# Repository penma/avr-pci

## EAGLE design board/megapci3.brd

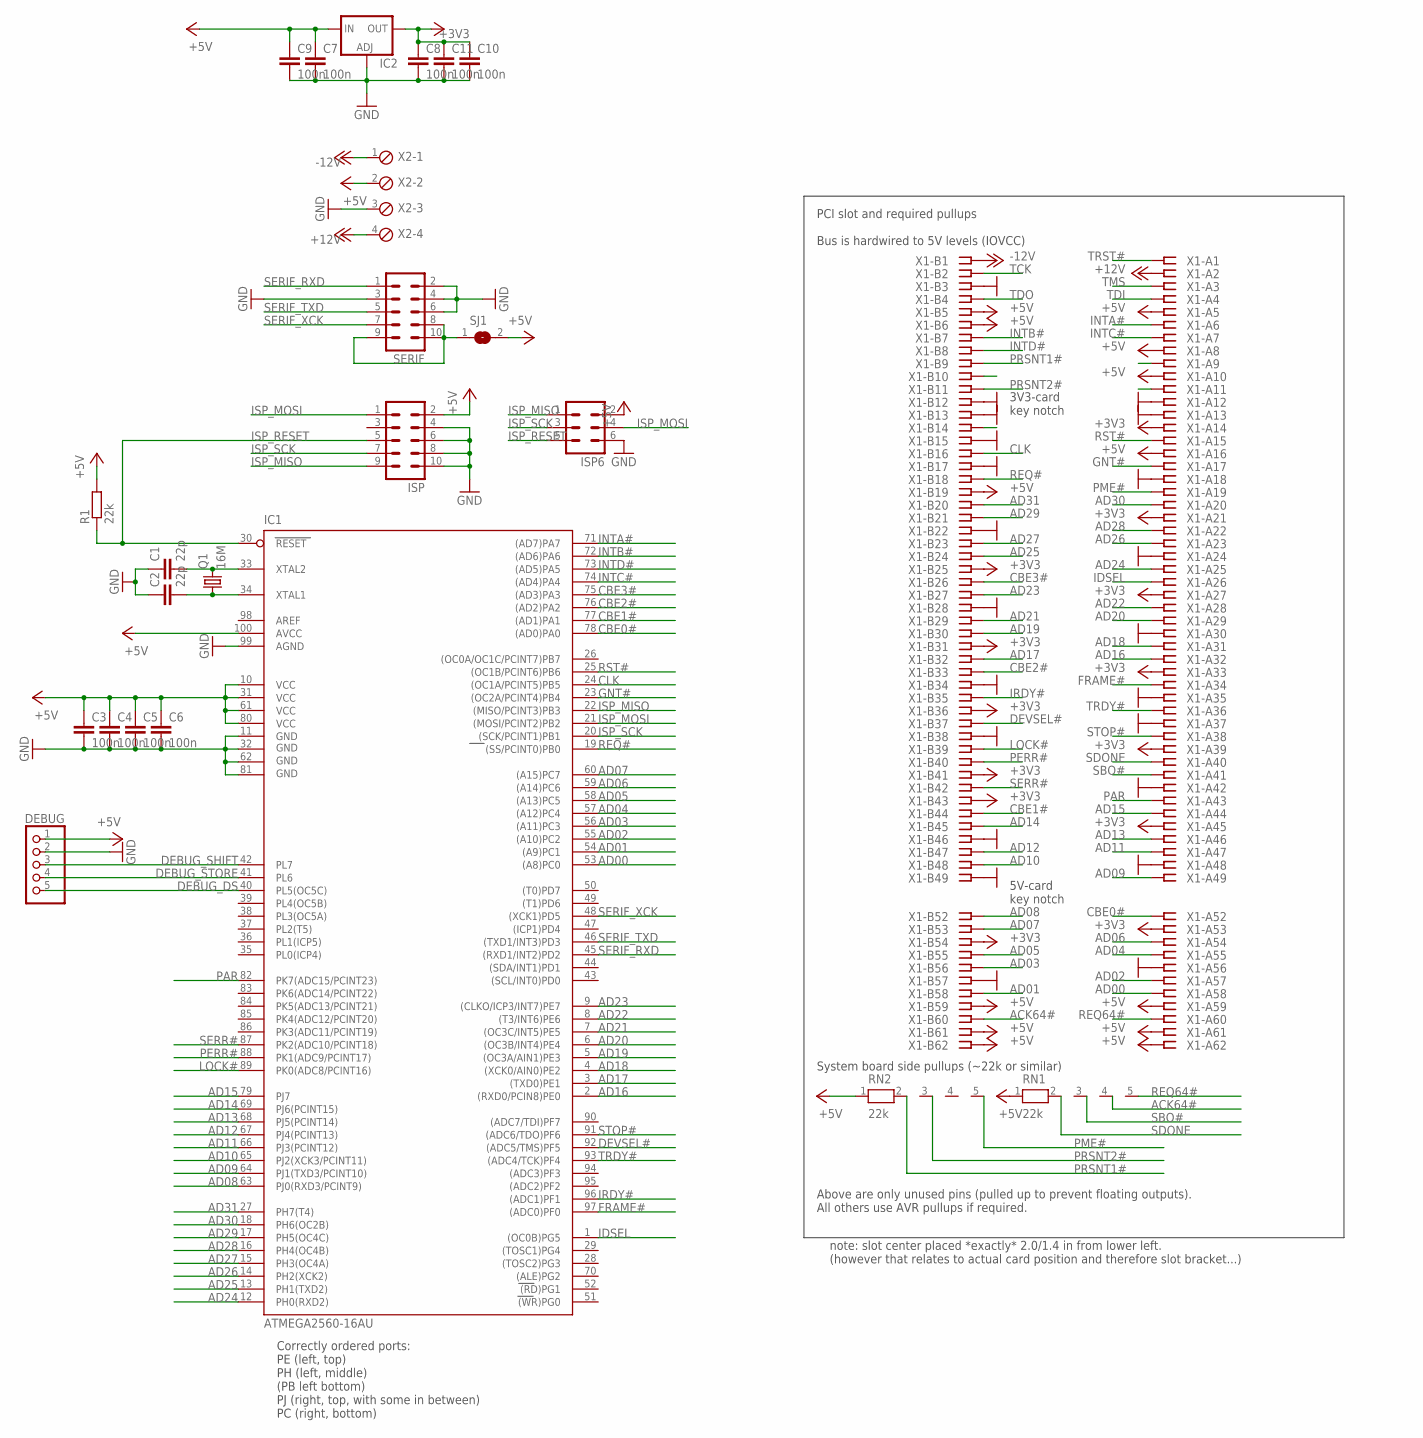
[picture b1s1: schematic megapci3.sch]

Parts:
C1, C2: 22p; C0805
C3, C4, C5, C6, C7, C8, C9, C10, C11: 100n; C0805
DEBUG: PINHD-1X5; 1X05
IC1: ATMEGA2560-16AU; TQFP100
IC2: LM317TS; 317TS
ISP: ML10
ISP6: ML6
Q1: 16M; HC49/S
R1: 22k; R0805
RN1, RN2: 22k; RN-5
SERIF: ML10
SJ1: SJ
X1: PCI-SLOT; CON-PCI
X2: MPT4; 4POL254

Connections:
5V-SER: SERIF.8, SERIF.9, SERIF.10, SJ1.1
+3V3: C8.1, C10.1, C11.1, IC2.2 (OUT), X1.A14, X1.A21, X1.A27, X1.A33, X1.A39, X1.A45, X1.A53, X1.B25, X1.B31, X1.B36, X1.B41, X1.B43, X1.B54
+5V: C3.1, C4.1, C5.1, C6.1, C7.1, C9.1, DEBUG.1, IC1.10 (VCC), IC1.31 (VCC1), IC1.61 (VCC2), IC1.80 (VCC3), IC1.100 (AVCC), IC2.3 (IN), ISP.2, ISP6.2, R1.2, RN1.1, RN2.1, SJ1.2, X1.A5, X1.A8, X1.A10, X1.A16, X1.A59, X1.A61, X1.A62, X1.B5, X1.B6, X1.B19, X1.B59, X1.B61, X1.B62, X2.2
+12V: X1.A2, X2.4
-12V: X1.B1, X2.1
ACK64#: RN1.4, X1.B60
AD00: IC1.53 ((A8)PC0), X1.A58
AD01: IC1.54 ((A9)PC1), X1.B58
AD02: IC1.55 ((A10)PC2), X1.A57
AD03: IC1.56 ((A11)PC3), X1.B56
AD04: IC1.57 ((A12)PC4), X1.A55
AD05: IC1.58 ((A13)PC5), X1.B55
AD06: IC1.59 ((A14)PC6), X1.A54
AD07: IC1.60 ((A15)PC7), X1.B53
AD08: IC1.63 (PJ0(RXD3/PCINT9)), X1.B52
AD09: IC1.64 (PJ1(TXD3/PCINT10)), X1.A49
AD10: IC1.65 (PJ2(XCK3/PCINT11)), X1.B48
AD11: IC1.66 (PJ3(PCINT12)), X1.A47
AD12: IC1.67 (PJ4(PCINT13)), X1.B47
AD13: IC1.68 (PJ5(PCINT14)), X1.A46
AD14: IC1.69 (PJ6(PCINT15)), X1.B45
AD15: IC1.79 (PJ7), X1.A44
AD16: IC1.2 ((RXD0/PCIN8)PE0), X1.A32
AD17: IC1.3 ((TXD0)PE1), X1.B32
AD18: IC1.4 ((XCK0/AIN0)PE2), X1.A31
AD19: IC1.5 ((OC3A/AIN1)PE3), X1.B30
AD20: IC1.6 ((OC3B/INT4)PE4), X1.A29
AD21: IC1.7 ((OC3C/INT5)PE5), X1.B29
AD22: IC1.8 ((T3/INT6)PE6), X1.A28
AD23: IC1.9 ((CLKO/ICP3/INT7)PE7), X1.B27
AD24: IC1.12 (PH0(RXD2)), X1.A25
AD25: IC1.13 (PH1(TXD2)), X1.B24
AD26: IC1.14 (PH2(XCK2)), X1.A23
AD27: IC1.15 (PH3(OC4A)), X1.B23
AD28: IC1.16 (PH4(OC4B)), X1.A22
AD29: IC1.17 (PH5(OC4C)), X1.B21
AD30: IC1.18 (PH6(OC2B)), X1.A20
AD31: IC1.27 (PH7(T4)), X1.B20
CBE0#: IC1.78 ((AD0)PA0), X1.A52
CBE1#: IC1.77 ((AD1)PA1), X1.B44
CBE2#: IC1.76 ((AD2)PA2), X1.B33
CBE3#: IC1.75 ((AD3)PA3), X1.B26
CLK: IC1.24 ((OC1A/PCINT5)PB5), X1.B16
DEBUG_DS: DEBUG.5, IC1.40 (PL5(OC5C))
DEBUG_SHIFT: DEBUG.3, IC1.42 (PL7)
DEBUG_STORE: DEBUG.4, IC1.41 (PL6)
DEVSEL#: IC1.92 ((ADC5/TMS)PF5), X1.B37
FRAME#: IC1.97 ((ADC0)PF0), X1.A34
GND: C1.1, C2.1, C3.2, C4.2, C5.2, C6.2, C7.2, C8.2, C9.2, C10.2, C11.2, DEBUG.2, IC1.11 (GND), IC1.32 (GND1), IC1.62 (GND2), IC1.81 (GND3), IC1.99 (AGND), IC2.1 (ADJ), ISP.4, ISP.6, ISP.8, ISP.10, ISP6.6, SERIF.2, SERIF.3, SERIF.4, SERIF.6, X1.A12, X1.A13, X1.A18, X1.A24, X1.A30, X1.A35, X1.A37, X1.A42, X1.A48, X1.A56, X1.B3, X1.B12, X1.B13, X1.B15, X1.B17, X1.B22, X1.B28, X1.B34, X1.B38, X1.B46, X1.B49, X1.B57, X2.3
GNT#: IC1.23 ((OC2A/PCINT4)PB4), X1.A17
IDSEL: IC1.1 ((OC0B)PG5), X1.A26
INTA#: IC1.71 ((AD7)PA7), X1.A6
INTB#: IC1.72 ((AD6)PA6), X1.B7
INTC#: IC1.74 ((AD4)PA4), X1.A7
INTD#: IC1.73 ((AD5)PA5), X1.B8
IRDY#: IC1.96 ((ADC1)PF1), X1.B35
ISP_MISO: IC1.22 ((MISO/PCINT3)PB3), ISP.9, ISP6.1
ISP_MOSI: IC1.21 ((MOSI/PCINT2)PB2), ISP.1, ISP6.4
ISP_RESET: IC1.30 (RESET), ISP.5, ISP6.5, R1.1
ISP_SCK: IC1.20 ((SCK/PCINT1)PB1), ISP.7, ISP6.3
LOCK#: IC1.89 (PK0(ADC8/PCINT16)), X1.B39
unnamed: C1.2, IC1.33 (XTAL2), Q1.2
unnamed: C2.2, IC1.34 (XTAL1), Q1.1
PAR: IC1.82 (PK7(ADC15/PCINT23)), X1.A43
PERR#: IC1.88 (PK1(ADC9/PCINT17)), X1.B40
PME#: RN2.5, X1.A19
PRSNT1#: RN2.2, X1.B9
PRSNT2#: RN2.3, X1.B11
REQ64#: RN1.5, X1.A60
REQ#: IC1.19 ((SS/PCINT0)PB0), X1.B18
RST#: IC1.25 ((OC1B/PCINT6)PB6), X1.A15
RSVD1: X1.A9
RSVD2: X1.A11
RSVD3: X1.B10
RSVD4: X1.B14
SBO#: RN1.3, X1.A41
SDONE: RN1.2, X1.A40
SERIF_RXD: IC1.45 ((RXD1/INT2)PD2), SERIF.1
SERIF_TXD: IC1.46 ((TXD1/INT3)PD3), SERIF.5
SERIF_XCK: IC1.48 ((XCK1)PD5), SERIF.7
SERR#: IC1.87 (PK2(ADC10/PCINT18)), X1.B42
STOP#: IC1.91 ((ADC6/TDO)PF6), X1.A38
TCK: X1.B2
TDI: X1.A4
TDO: X1.B4
TMS: X1.A3
TRDY#: IC1.93 ((ADC4/TCK)PF4), X1.A36
TRST#: X1.A1

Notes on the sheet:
3V3-card key notch
5V-card key notch
PCI slot and required pullups Bus is hardwired to 5V levels (IOVCC)
System board side pullups (~22k or similar)
Above are only unused pins (pulled up to prevent floating outputs). All others use AVR pullups if required.
Correctly ordered ports: PE (left, top) PH (left, middle) (PB left bottom) PJ (right, top, with some in between) PC (right, bottom)
note: slot center placed *exactly* 2.0/1.4 in from lower left. (however that relates to actual card position and therefore slot bracket...)

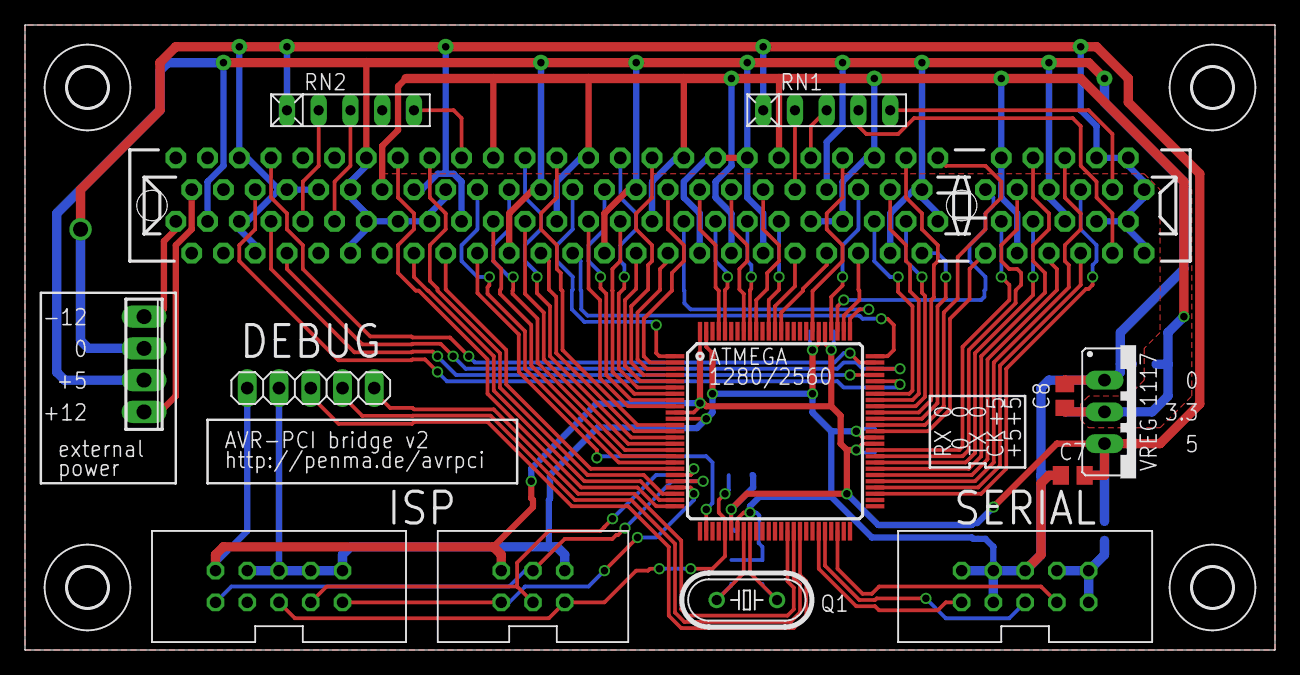
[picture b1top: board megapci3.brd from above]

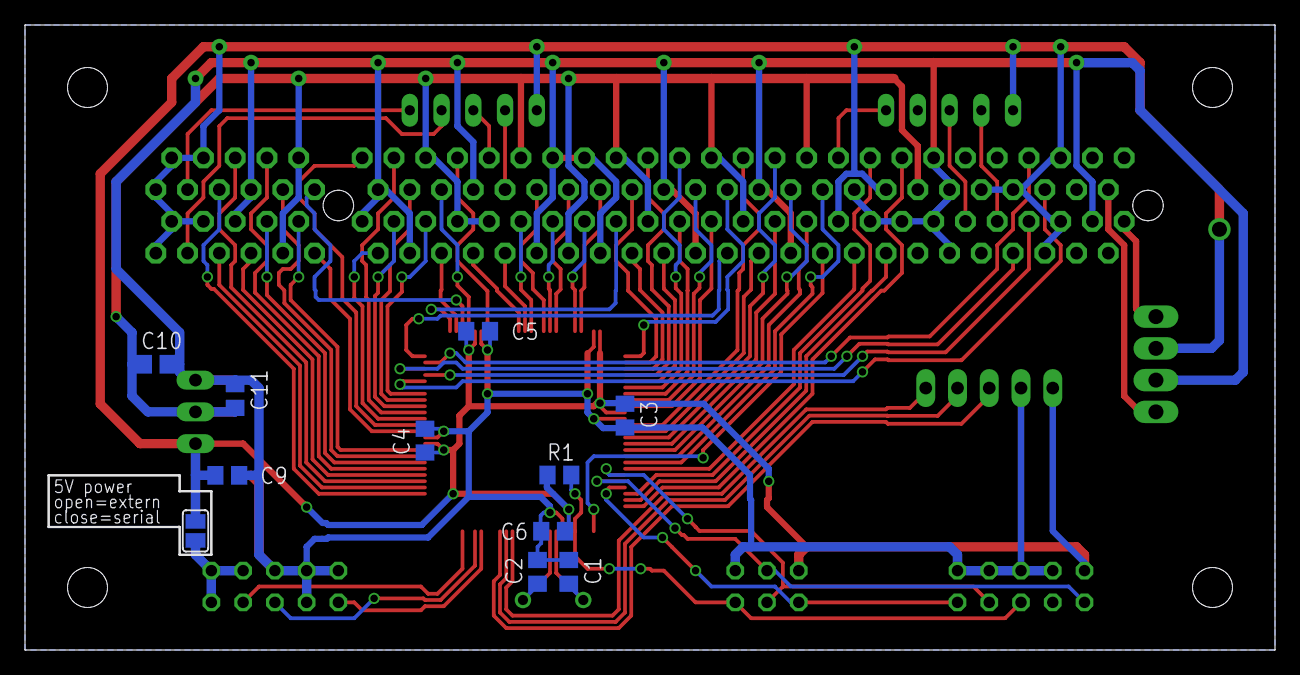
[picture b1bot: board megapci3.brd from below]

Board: 2 copper layers, 100.0 x 50.0 mm, 28 parts (11 on the bottom side), 79 nets.

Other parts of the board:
U$1, U$2, U$3, U$4: 3,2

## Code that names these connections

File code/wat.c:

#include <avr/io.h>
#include <stdint.h>
#include "console.h"

#define panic(m) do { console_fstr(m); while (1) { } } while (0)

static inline void clk_high() __attribute__((always_inline));
static inline void clk_high() {
	PORTB |= 1 << 5;
}

static inline void clk_low() __attribute__((always_inline));
static inline void clk_low() {
	PORTB &= ~(1 << 5);
}

/* port F control signals */
#define FRAME   (1 << 0)
#define IRDY    (1 << 1)
#define TRDY    (1 << 4)
#define DEVSEL  (1 << 5)
#define STOP    (1 << 6)

/* a signal is asserted by
 * disabling the pullup (this causes the signal to be driven high for a moment)
 * driving it low
 */
#define assert_signal(s) do { DDRF |= (s); PORTF &= ~(s); } while (0)
/* deasserting is a two-step process
 * in the first PCI clock cycle the pin is driven high
 * one cycle later, stop driving it and only have the pullup
 */
#define deassert_signal_1(s) do { PORTF |= (s); } while (0)
#define deassert_signal_2(s) do { DDRF &= ~(s); } while (0)

#define is_signal_asserted(s) (!(PINF | (s)))

static inline void idsel_high() {
	PORTG |= 1 << 5;
}

static inline void idsel_low() {
	PORTG &= ~(1 << 5);
}

static void ad_output_mode() {
	DDRC = DDRE = DDRH = DDRJ = 0xff;
}

static void ad_tristate() {
	DDRC = DDRE = DDRH = DDRJ = 0x00;
	PORTC = PORTE = PORTH = PORTJ = 0x00;
}

static void ad_set(uint32_t v) {
	/* TODO check endianness and swap stuff around if needed */
	PORTC = v & 0xff;
	PORTJ = (v >> 8) & 0xff;
	PORTE = (v >> 16) & 0xff;
	PORTH = (v >> 24) & 0xff;
}

static uint32_t ad_get() {
	/* TODO endianness, see above */
	return PORTC | ((uint32_t)PORTJ << 8) | ((uint32_t)PORTE << 16) | ((uint32_t)PORTH << 24);
}

static void par_output_mode() {
	DDRK |= 1 << 7;
}

static void par_tristate() {
	DDRK &= ~(1 << 7);
	PORTK &= ~(1 << 7);
}

static void par_set(uint8_t v) {
	if (v) {
		PORTK |= 1 << 7;
	} else {
		PORTK &= ~(1 << 7);
	}
}

static inline uint8_t par_get() {
	return PINK & (1 << 7);
}

static void cbe_output_mode() {
	DDRA |= 0x0f;
}

static void cbe_tristate() {
	DDRA &= ~(0x0f);
	PORTA &= ~(0x0f);
}

static void cbe_set(uint8_t v) {
	PORTA &= ~(0x0f);
	PORTA |= (v & 0xf);
}

uint8_t ad_cbe_parity(uint32_t addr, uint8_t cbe) {
	/* even number of ones in addr, cbe, par */
	return __builtin_parity(addr) ^ __builtin_parity(cbe);
}

static void sanity_deasserted_devsel_trdy() {
	/* sanity check: DEVSEL and TRDY should now be deasserted */
	if (is_signal_asserted(DEVSEL) || is_signal_asserted(TRDY)) {
		panic("DEVSEL or TRDY still asserted");
	}
}

static void sanity_deasserted_frame_irdy() {
	/* sanity check: FRAME and IRDY should not be asserted because the
	 * bus is idle */
	if (is_signal_asserted(FRAME) || is_signal_asserted(IRDY)) {
		panic("FRAME or IRDY asserted on idle bus");
	}
}


uint32_t master_read(uint32_t addr, uint8_t cmd, uint8_t be) {
	sanity_deasserted_frame_irdy();

	/* Address phase */

	clk_high();
	clk_low();
	assert_signal(FRAME);
	idsel_high();

	ad_output_mode();
	ad_set(addr);
	cbe_output_mode();
	cbe_set(cmd);
	uint8_t addr_par = ad_cbe_parity(addr, cmd);

	/* turnaround cycle */

	clk_high();
	ad_tristate();
	clk_low();
	assert_signal(IRDY);
	deassert_signal_1(FRAME);
	idsel_low();

	par_output_mode();
	par_set(addr_par);
	cbe_set(be);

	/* wait for DEVSEL to be asserted */
	int c = 4;
	while (!is_signal_asserted(DEVSEL)) {
		clk_high();
		par_tristate();
		clk_low();
		c--;

		if (c == 0) {
			goto master_abort;
		}
	}

	/* wait for TRDY to be asserted */
	c = 12;
	while (!is_signal_asserted(TRDY)) {
		if (is_signal_asserted(STOP)) {
			if (is_signal_asserted(DEVSEL)) {
				goto retry;
			} else {
				goto target_abort;
			}
		}

		clk_high();
		par_tristate();
		clk_low();
		c--;

		if (c == 0) {
			/* actually not a master abort, but we handle it
			 * exactly like one.
			 * (not sure if this can actually happen according to
			 * the spec, but it's a good idea to have some kind of
			 * timeout here...)
			 */
			goto master_abort;
		}
	}

	/* TRDY is asserted and as we have previously asserted IRDY, a data
	 * phase is about to happen
	 */
	uint32_t adval = ad_get();
	clk_high();
	par_tristate();
	deassert_signal_1(IRDY);
	deassert_signal_2(FRAME);
	cbe_tristate();
	clk_low();

	/* target should now also return bus to idle
	 * target also provides parity for the data word */
	uint8_t adval_par = par_get();
	clk_high();
	deassert_signal_2(IRDY);
	clk_low();

	/* TODO: verify parity of received data word against that of the PAR pin */

	sanity_deasserted_devsel_trdy();

	return adval;

master_abort:
target_abort:
	deassert_signal_1(IRDY);
	deassert_signal_1(FRAME);
	cbe_tristate();
	clk_high();
	deassert_signal_2(IRDY);
	deassert_signal_2(FRAME);
	clk_low();

	sanity_deasserted_devsel_trdy();

	return 0xffffffff;

retry:
	/* TODO */
	panic("Target requested Retry but this is unimplemented");
}





volatile uint32_t dummyaddr;
volatile uint8_t cbedummy;
void main() {
	while (1) {
		master_read(dummyaddr, cbedummy, 0xf);
	}
}

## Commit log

2015-12-18 initial
2015-12-20 towards unifying master_read/write
2015-12-20 master_read and master_write now merged into master_transaction
2015-12-20 make IDSEL always high
    As we only have a single slot and IDSEL is just for identifying one of
    many slots during configuration transactions (and otherwise ignored) we
    can just permanently select the one and only IDSEL line.
2015-12-20 slight always_inline cleanup
2015-12-21 Timer 3 can now be used for benchmarking
    Use TCNT3 to get a cycle counter
2015-12-22 improved support for timing
2015-12-22 improved device identification
2015-12-24 inform us when device requests the bus
2015-12-25 bugfix; move PCI parts to subdir; start rtl8169 driver
    bugfix: GNT# was driven as if it was GNT. That is, actually granting the
    card the bus all the time. This obviously causes the card to do funny things
    when it sees its GNT# asserted and someone else is on the bus...
2015-12-25 separate pci identification into its own "driver"
2016-01-11 various changes
    * start of rtl8139 driver
    * debug port moved to ISP port (hardware SPI not used because the SS pin is
    used, which prevents proper SPI master operation)
    * identify more PCI devices
    * timer-controlled PCI clock when no transaction is active (some chips need
    an active clock or they stop doing anything at all)
